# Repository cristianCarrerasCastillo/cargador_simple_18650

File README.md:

# cargador_simple_18650
cargador para 1 celda de bateria 18650, con posibilidad de alimentación usb, con indicador de termino de carga

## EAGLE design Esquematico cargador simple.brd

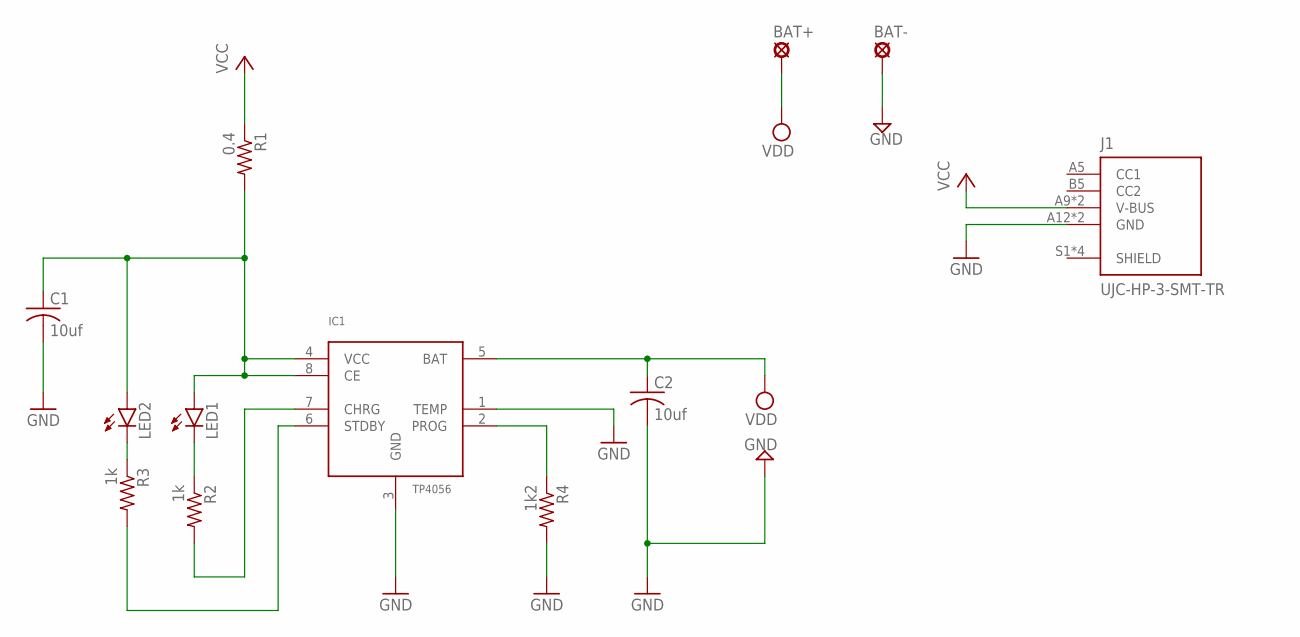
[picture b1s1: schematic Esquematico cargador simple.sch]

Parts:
BAT+: LSP10
BAT-: LSP10
C1, C2: 10uf; C1206
IC1: TP4056; SOP-8
J1: UJC-HP-3-SMT-TR; CUI_UJC-HP-3-SMT-TR
LED1, LED2: LEDSML1206; SML1206
R1: 0.4; R1206
R2, R3: 1k; R1206
R4: 1k2; R1206

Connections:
GND: BAT-.MP, C1.2, C2.2, IC1.1 (TEMP), IC1.3 (GND), J1.A12 (GND), J1.B12 (GND), R4.2
unnamed: C1.1, IC1.4 (VCC), IC1.8 (CE), LED1.A, LED2.A, R1.2
unnamed: IC1.2 (PROG), R4.1
unnamed: LED1.C, R2.1
unnamed: IC1.7 (CHRG), R2.2
unnamed: LED2.C, R3.1
unnamed: IC1.6 (STDBY), R3.2
VCC: J1.A9 (V-BUS), J1.B9 (V-BUS), R1.1
VDD: BAT+.MP, C2.1, IC1.5 (BAT)

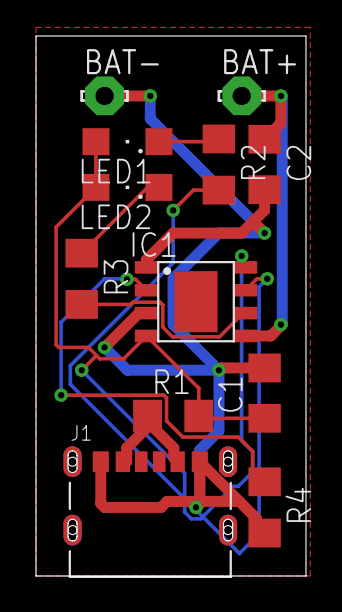
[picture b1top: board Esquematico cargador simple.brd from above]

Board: 2 copper layers, 15.0 x 30.0 mm, 12 parts (0 on the bottom side), 9 nets.

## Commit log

2020-12-26 creacion de repositorio
2020-12-26 creacion de esquematico y pcb con los componentes basicos y un usb
